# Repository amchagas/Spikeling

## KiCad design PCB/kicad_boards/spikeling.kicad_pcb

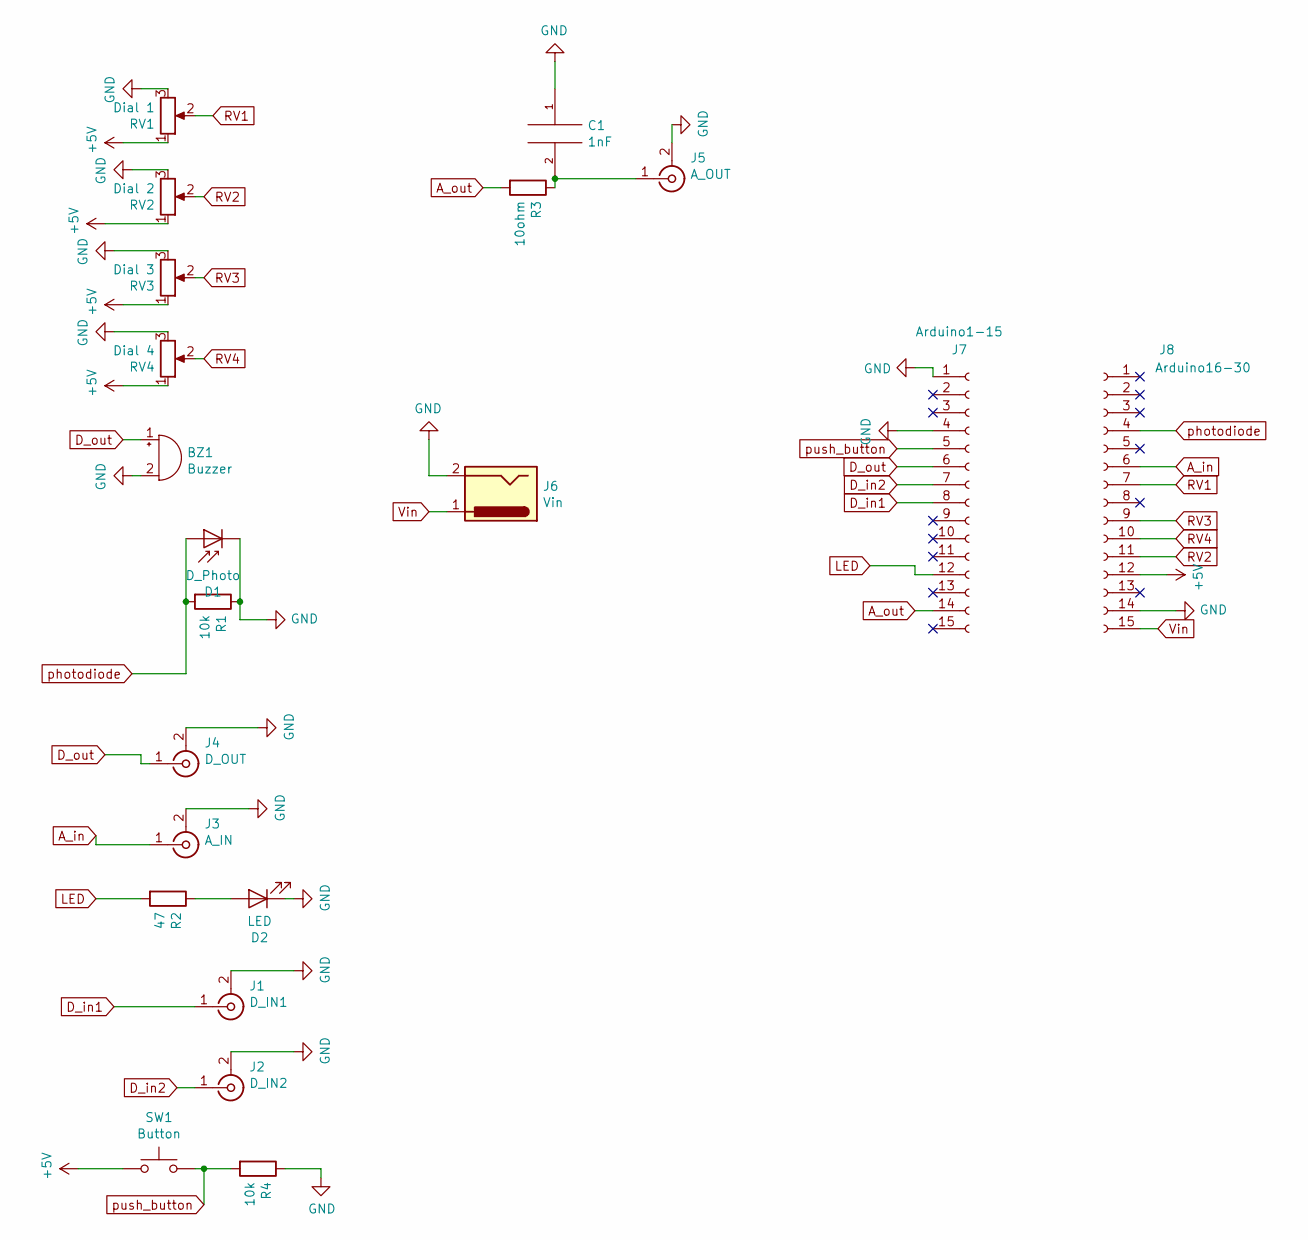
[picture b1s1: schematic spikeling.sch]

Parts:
BZ1: Buzzer; Buzzer_Murata_PKMCS0909E4000-R1
C1: 1nF; C_1206_3216Metric_Pad1.42x1.75mm_HandSolder
D1: D_Photo; LED_1806_4516Metric
D2: LED; LED_1210_3225Metric_Pad1.42x2.65mm_HandSolder
J1: D_IN1; BNC_TEConnectivity_1478204_Vertical
J2: D_IN2; BNC_TEConnectivity_1478204_Vertical
J3: A_IN; BNC_TEConnectivity_1478204_Vertical
J4: D_OUT; BNC_TEConnectivity_1478204_Vertical
J5: A_OUT; BNC_TEConnectivity_1478204_Vertical
J6: Vin; BarrelJack_Horizontal
J7: Arduino1-15; PinHeader_1x15_P2.54mm_Vertical
J8: Arduino16-30; PinHeader_1x15_P2.54mm_Vertical
R1, R4: 10k; R_1206_3216Metric_Pad1.42x1.75mm_HandSolder
R2: 47; R_1206_3216Metric_Pad1.42x1.75mm_HandSolder
R3: 10ohm; R_1206_3216Metric_Pad1.42x1.75mm_HandSolder
RV1: Dial 1; Potentiometer_Alps_RK09L_Single_Vertical
RV2: Dial 2; Potentiometer_Alps_RK09L_Single_Vertical
RV3: Dial 3; Potentiometer_Alps_RK09L_Single_Vertical
RV4: Dial 4; Potentiometer_Alps_RK09L_Single_Vertical
SW1: Button; SW_Push_1P1T_NO_6x6mm_H9.5mm

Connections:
+5V: J8.12, RV1.1, RV2.1, RV3.1, RV4.1, SW1.1
A_in: J3.1 (In), J8.6
A_out: J7.14, R3.2
D_in1: J1.1 (In), J7.8
D_in2: J2.1 (In), J7.7
D_out: BZ1.1 (-), J4.1 (In), J7.6
GND: BZ1.2 (+), C1.1, D1.1 (K), D2.1 (K), J1.2 (Ext), J2.2 (Ext), J3.2 (Ext), J4.2 (Ext), J5.2 (Ext), J6.2, J7.1, J7.4, J8.14, R1.1, R4.1, RV1.3, RV2.3, RV3.3, RV4.3
LED: J7.12, R2.2
unnamed: C1.2, J5.1 (In), R3.1
unnamed: D2.2 (A), R2.1
RV1: J8.7, RV1.2
RV2: J8.11, RV2.2
RV3: J8.9, RV3.2
RV4: J8.10, RV4.2
Vin: J6.1, J8.15
photodiode: D1.2 (A), J8.4, R1.2
push_button: J7.5, R4.2, SW1.2

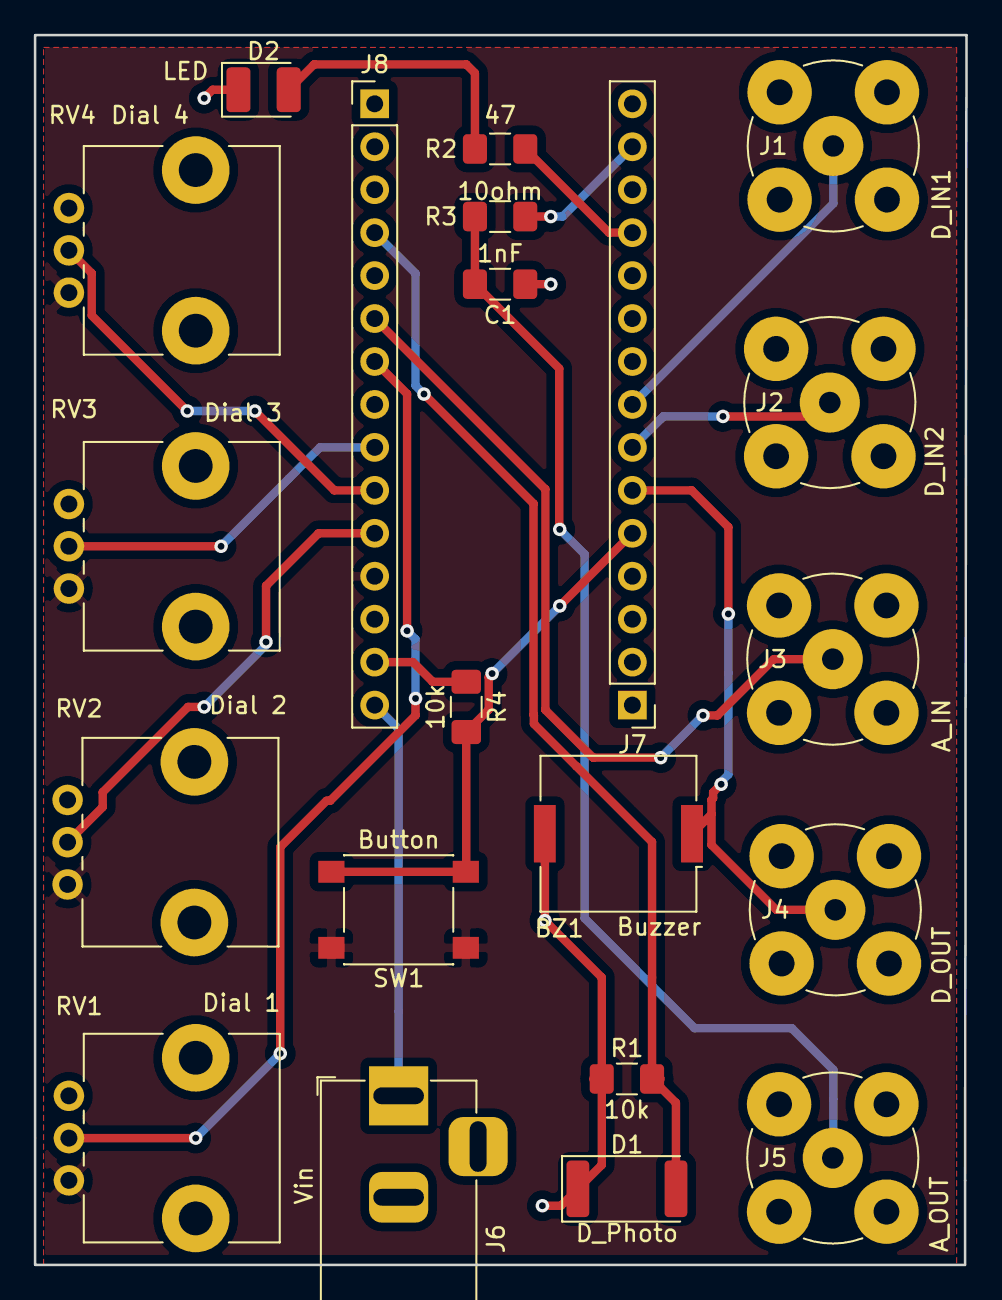
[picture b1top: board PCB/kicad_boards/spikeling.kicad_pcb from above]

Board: 2 copper layers, 55.1 x 72.7 mm, 21 parts (0 on the bottom side), 17 nets.

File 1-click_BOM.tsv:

References,Qty,Description,Manufacturer,MPN,Manufacturer_1,MPN_2,Digikey,Mouser,RS,Newark,Farnell
MCU,1,Arduino Nano,Arduino,A000087,Arduino,A000005 ,,,696-1667,,
J8,2,Headers 15 pin 1 row,Samtec inc,SSA-115-S-T ,Samtec Inc,SSW-115-01-T-S ,,,180-4101,,
RV1;RV2;RV3;RV4,4,10k/50mw/20%,Alps,RK09K1130AH1 ,,,,,729-3587,,
BZ1,1,25V 75dB,Murata,PKMCS0909E4000-R1,,,,,167-5001,,
J1;J2;J3;J4;J5,5,female PCB conn,RS pro,546-4027,,,,,546-4027,,
SW1,1,12V 50ma,TE connectivity,4-1437565-1,,,,,479-1508,,
D2,1,617nm 2V 20mA,BroadCom,HSMF-C155,,,,,486-0430,,
C1,1,100V 1nf 5%,Kemet,C1206C102KDRACTU,,,,,500-2528,,
"R1,R4",2,250V 10k 250mW 1%,Vishay,CRCW120610K0FKEA,,,,,679-1765,,
R2,1,250V 47ohm 250mW 1%,TE connectivity,CRG1206F47R,,,,,223-2085,,
R3,1,250V 10ohm 250mW 1%,TE connectivity,CRG1206F10R,,,,,223-1997,,
D1,1,visible spectrum,Osram,BP 104 S-Z,,,,,654-8148,,
J6,1,Barrel Jack,Cliff,FC68148 DC10A,,,,,,,

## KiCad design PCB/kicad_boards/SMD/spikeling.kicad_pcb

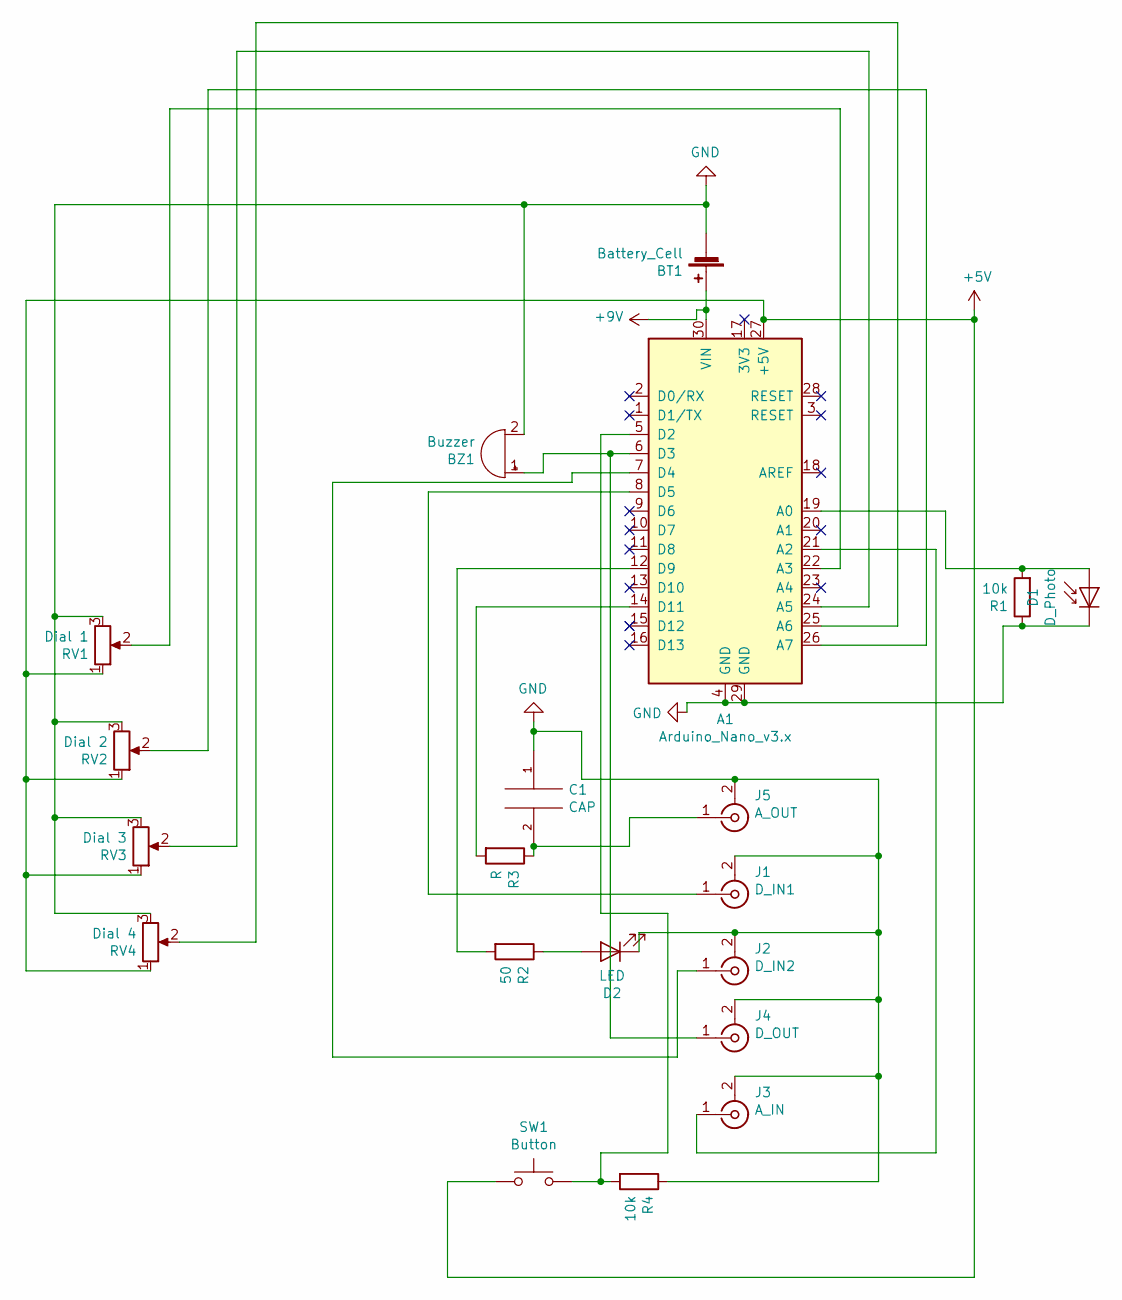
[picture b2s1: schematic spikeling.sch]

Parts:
A1: Arduino_Nano_v3.x; Arduino_Nano
BT1: Battery_Cell; BatteryHolder_Eagle_12BH611-GR
BZ1: Buzzer; Buzzer_12x9.5RM7.6
C1: CAP; C_Disc_D3.0mm_W2.0mm_P2.50mm
D1: D_Photo; LED_D5.0mm_Clear
D2: LED; LED_D8.0mm
J1: D_IN1; BNC_TEConnectivity_1478204_Vertical
J2: D_IN2; BNC_TEConnectivity_1478204_Vertical
J3: A_IN; BNC_TEConnectivity_1478204_Vertical
J4: D_OUT; BNC_TEConnectivity_1478204_Vertical
J5: A_OUT; BNC_TEConnectivity_1478204_Vertical
R1, R4: 10k; R_Axial_DIN0207_L6.3mm_D2.5mm_P10.16mm_Horizontal
R2: 50; R_Axial_DIN0207_L6.3mm_D2.5mm_P10.16mm_Horizontal
R3: R; R_Axial_DIN0207_L6.3mm_D2.5mm_P10.16mm_Horizontal
RV1: Dial 1; Potentiometer_Alps_RK09L_Single_Vertical
RV2: Dial 2; Potentiometer_Alps_RK09L_Single_Vertical
RV3: Dial 3; Potentiometer_Alps_RK09L_Single_Vertical
RV4: Dial 4; Potentiometer_Alps_RK09L_Single_Vertical
SW1: Button; SW_PUSH-12mm

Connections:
+5V: A1.27 (+5V), RV1.1, RV2.1, RV3.1, RV4.1, SW1.1
+9V: A1.30 (VIN), BT1.1 (+)
GND: A1.4 (GND), A1.29 (GND), BT1.2 (-), BZ1.2 (+), C1.1, D1.1 (K), D2.1 (K), J1.2 (Ext), J2.2 (Ext), J3.2 (Ext), J4.2 (Ext), J5.2 (Ext), R1.1, R4.1, RV1.3, RV2.3, RV3.3, RV4.3
unnamed: A1.5 (D2), R4.2, SW1.2
unnamed: A1.6 (D3), BZ1.1 (-), J4.1 (In)
unnamed: A1.7 (D4), J2.1 (In)
unnamed: A1.8 (D5), J1.1 (In)
unnamed: A1.12 (D9), R2.2
unnamed: A1.14 (D11), R3.2
unnamed: A1.19 (A0), D1.2 (A), R1.2
unnamed: A1.21 (A2), J3.1 (In)
unnamed: A1.22 (A3), RV1.2
unnamed: A1.24 (A5), RV3.2
unnamed: A1.25 (A6), RV4.2
unnamed: A1.26 (A7), RV2.2
unnamed: C1.2, J5.1 (In), R3.1
unnamed: D2.2 (A), R2.1

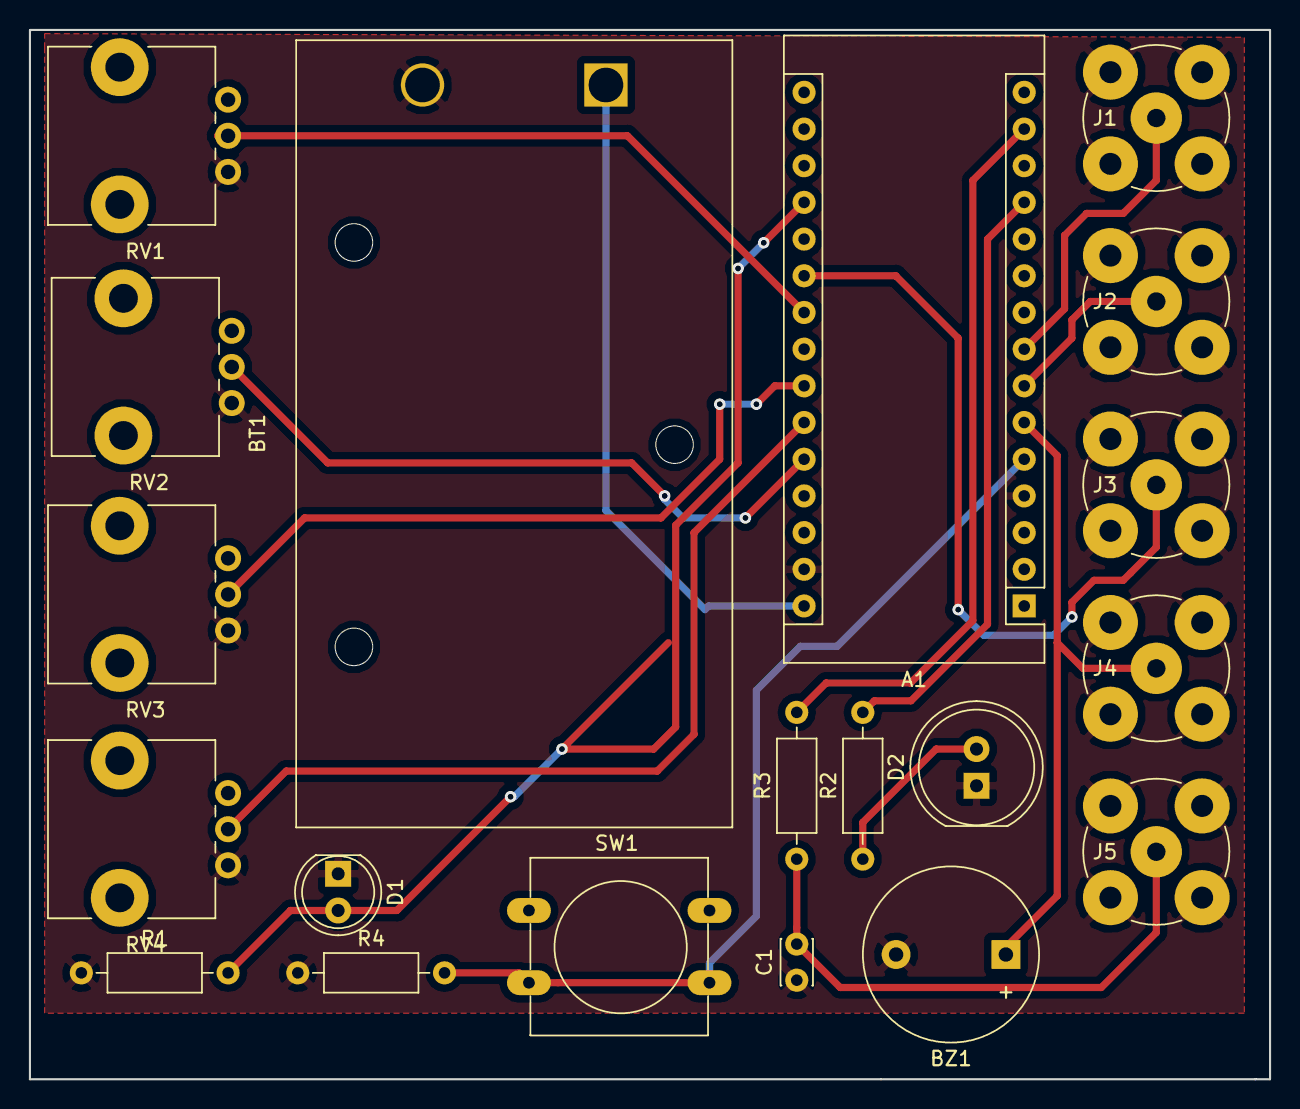
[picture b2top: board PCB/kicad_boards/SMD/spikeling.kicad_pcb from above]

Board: 2 copper layers, 85.9 x 72.6 mm, 20 parts (0 on the bottom side), 17 nets.

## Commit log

2020-05-05 organize repo
2020-05-05 organize repo, port kicad boards
2020-05-17 create SMD board
2020-06-08 update smd version of board
2020-07-09 more work on smd board
2020-07-16 update SMD board
2021-04-26 modified kicad pcb

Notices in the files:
PCB/kicad_boards/spikeling.kicad_pcb:
CERN OHL-S v2.0
